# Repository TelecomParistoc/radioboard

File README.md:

# RadioBoard

Design d'une carte électronique permettant de d'échanger des messages et de localiser les robots

## Définition des acteurs

On distingue 3 types d'acteurs aux besoins différents :

* les robots, où la radio se comporte comme un esclave piloté par le raspberry pi et autres composants
* les balise sur les robots adverses, où la radio est indépendante et doit envoyer les mesures aux robots
* les balises fixes, où la radio est indépendante et peut communiquer avec un ordinateur pour le debug

Pour des raisons d'efficacité, il a été décidé de ne concevoir qu'une seule carte, adaptée aux besoins de tous les acteurs.

## Vue système

### Système robot

Il est nécessaire de fournir 3 ports :

* Un port esclave sur le bus I2C principal du robot, permettant la communication avec le Raspberry Pi
* Un port esclave SPI pour une liaison direct rapide à faible latence avec la carte de contrôle des moteurs
* Un port série pour ouvrir un terminal série à distance sur le Raspberry Pi contrôlé depuis une balise fixe en cas de perte de la connexion WiFi (environnement difficile pendant la coupe)

Par ailleurs, l'alimentation qui sera fournie à la carte sera du 5V (en raison de la consommation importante des Decawaves, il est plus raisonnable de ne pas tirer sur le 3.3V du Raspberry Pi), elle devra donc être abaissée localement.

### Système balise

Dans les balises (fixes et sur les robots adverses), la carte radio est l'unique carte, et n'est accompagnée que d'une batterie. Elle doit donc être autonome.

La faisabilité d'un système interne de recharge doit être étudié. Dans tous les cas, le système doit pouvoir détecter la fin de décharge de la batterie afin d'éviter la destruction de celle-ci.

## Contraintes

#### RC1 Placement du module radio
Pour fonctionner correctement, le module radio DWM1000 doit être placé conformément aux contraintes de la datasheet du DWM1000 page 17.

#### RC2 Taille de la carte
Afin de pouvoir être embarqué dans les balises, la carte devra avoir des dimensions maximales de 70mmx70mm. De plus, il est important de minimiser la taille de la carte pour des raisons d'efficacité budgétaire. Il faut également prévoir le placement des batteries pour les balises, afin que le système total rentre dans un pavé de 80x80x80mm comme spécifié dans le règlement de la coupe de France de robotique.

#### RC3 Placement des connecteurs
Tout les connecteurs devront être placés de telle sorte qu'un câble connecté ne puisse pas se mettre dans le chemin du signal radio entre deux modules.

#### RC4 Programmation et debug de la carte
La programmation et le debug des cartes sera fait avec les sondes J-link du club en SWD et devra utiliser un connecteur comme [celui-ci](http://fr.farnell.com/samtec/shf-105-01-l-d-sm/embase-male-1-27mm-2x5-voies/dp/1885915).

#### RC5 Alimentation de la carte
L'alimentation de la carte se fera dans les robots en 5VDC et dans les balises directement depuis les batteries sans composant extérieur.

#### RC6 Technologie des batteries
Le règlement de la coupe de France de robotique interdit l'utilisation de batteries Li-Ion et Li-Po en dehors d'un sac de protection, dont les dimensions rendront l'intégration dans des balises difficile. Ces deux technologies sont donc exclues.

#### RC7 Configuration du connecteur I2C
Le connecteur I2C reliant la carte au bus principal et fournissant l'alimentation **5V** est un micromatch 6 pins et doit avoir la configuration suivante :

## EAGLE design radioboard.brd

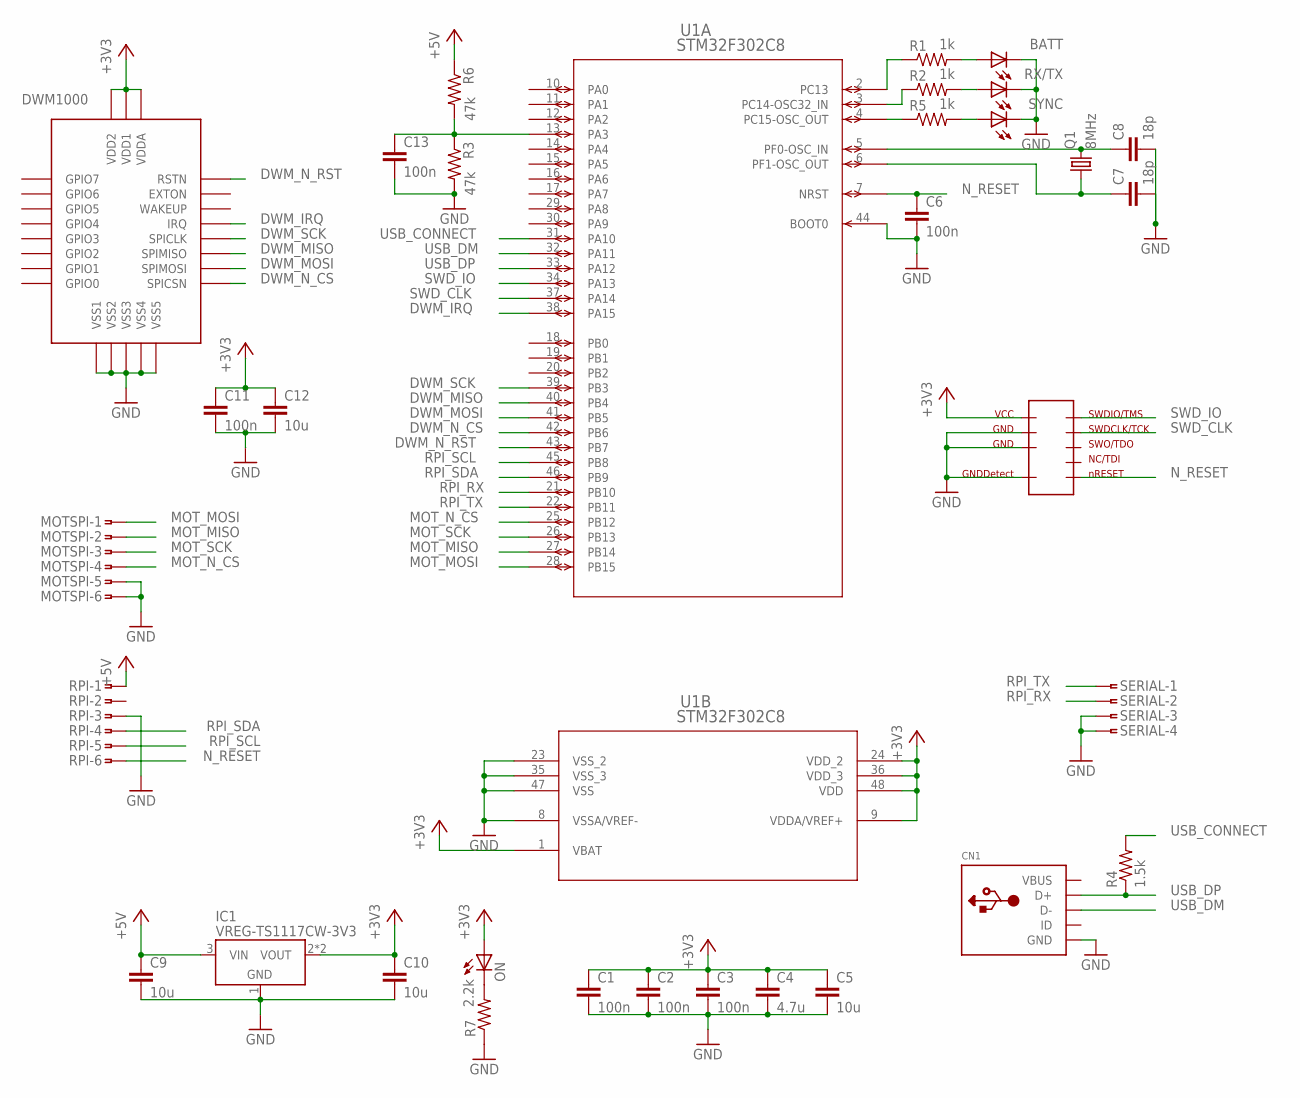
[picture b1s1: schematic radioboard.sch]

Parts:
BATT: LEDCHIPLED_0805; CHIPLED_0805
C1, C2, C3, C6, C11, C13: 100n; C0805
C4: 4.7u; C0805
C5, C9, C10, C12: 10u; C0805
C7, C8: 18p; C0805
CN1: USBMINIB; USB-MINIB
DWM1000: DWM1000; DW1000-PACKAGE
IC1: VREG-TS1117CW-3V3; SOT223
MOTSPI: SMDTOP-6; SMDTOP6
ON: LEDCHIPLED_0805; CHIPLED_0805
Q1: 8MHz; SM49
R1, R2, R5: 1k; M0805
R3, R6: 47k; M0805
R4: 1.5k; M0805
R7: 2.2k; M0805
RPI: SMDTOP-6; SMDTOP6
RX/TX: LEDCHIPLED_0805; CHIPLED_0805
SERIAL: SMDTOP-4; SMDTOP4
SYNC: LEDCHIPLED_0805; CHIPLED_0805
U1: STM32F302C8; LQFP48-7X7MM
U$1: SWD/JTAG-_PINS; SAMTEC_SHF-105-01-L-D-SM

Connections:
+3V3: C1.1, C2.1, C3.1, C4.1, C5.1, C10.1, C11.1, C12.1, DWM1000.VDD3V3 (VDD1), DWM1000.VDD3V32 (VDD2), DWM1000.VDDAON (VDDA), IC1.2 (VOUT), IC1.4 (VOUT), ON.A, U1.1 (VBAT), U1.9 (VDDA/VREF+), U1.24 (VDD_2), U1.36 (VDD_3), U1.48 (VDD), U$1.P$1
+5V: C9.1, IC1.3 (VIN), R6.1, RPI.1
DWM_IRQ: DWM1000.IRQ, U1.38 (PA15)
DWM_MISO: DWM1000.SPIMISO, U1.40 (PB4)
DWM_MOSI: DWM1000.SPIMOSI, U1.41 (PB5)
DWM_N_CS: DWM1000.SPICSN, U1.42 (PB6)
DWM_N_RST: DWM1000.RSTN, U1.43 (PB7)
DWM_SCK: DWM1000.SPICLK, U1.39 (PB3)
GND: BATT.C, C1.2, C2.2, C3.2, C4.2, C5.2, C6.2, C7.2, C8.2, C9.2, C10.2, C11.2, C12.2, C13.2, CN1.GND, DWM1000.VSS1, DWM1000.VSS2, DWM1000.VSS3, DWM1000.VSS4, DWM1000.VSS5, IC1.1 (GND), MOTSPI.5, MOTSPI.6, R3.2, R7.1, RPI.3, RX/TX.C, SERIAL.3, SERIAL.4, SYNC.C, U1.8 (VSSA/VREF-), U1.23 (VSS_2), U1.35 (VSS_3), U1.44 (BOOT0), U1.47 (VSS), U$1.P$3, U$1.P$5, U$1.P$9
MOT_MISO: MOTSPI.2, U1.27 (PB14)
MOT_MOSI: MOTSPI.1, U1.28 (PB15)
MOT_N_CS: MOTSPI.4, U1.25 (PB12)
MOT_SCK: MOTSPI.3, U1.26 (PB13)
unnamed: R1.1, U1.2 (PC13)
unnamed: C7.1, Q1.1, U1.6 (PF1-OSC_OUT)
unnamed: C8.1, Q1.2, U1.5 (PF0-OSC_IN)
unnamed: R2.1, U1.3 (PC14-OSC32_IN)
unnamed: R5.1, U1.4 (PC15-OSC_OUT)
unnamed: BATT.A, R1.2
unnamed: R2.2, RX/TX.A
unnamed: C13.1, R3.1, R6.2, U1.13 (PA3)
unnamed: ON.C, R7.2
unnamed: R5.2, SYNC.A
N_RESET: C6.1, RPI.6, U1.7 (NRST), U$1.P$10
RPI_RX: SERIAL.2, U1.21 (PB10)
RPI_SCL: RPI.5, U1.45 (PB8)
RPI_SDA: RPI.4, U1.46 (PB9)
RPI_TX: SERIAL.1, U1.22 (PB11)
SWD_CLK: U1.37 (PA14), U$1.P$4
SWD_IO: U1.34 (PA13), U$1.P$2
USB_CONNECT: R4.2, U1.31 (PA10)
USB_DM: CN1.D-, U1.32 (PA11)
USB_DP: CN1.D+, R4.1, U1.33 (PA12)
VBUS: CN1.VBUS

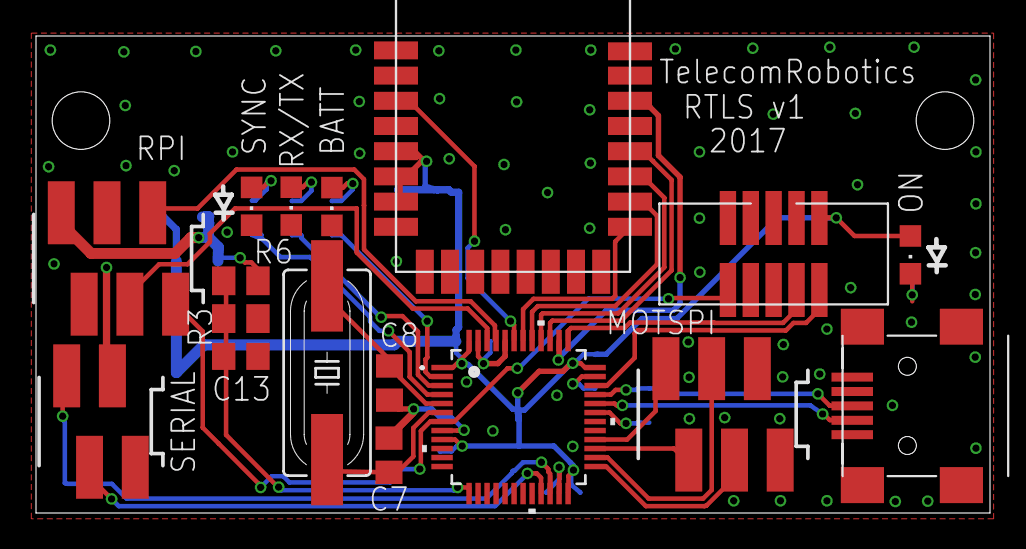
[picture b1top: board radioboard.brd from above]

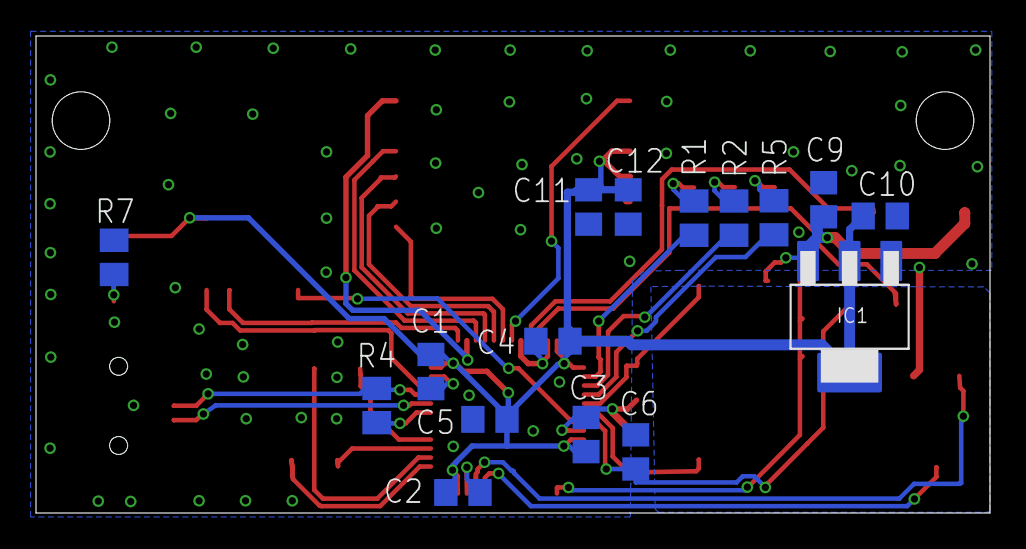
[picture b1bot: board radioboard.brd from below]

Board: 2 copper layers, 53.0 x 26.5 mm, 33 parts (16 on the bottom side), 33 nets.

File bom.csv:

Qty,Qty to buy,Value,Device,Package,Parts,Description, Farnell reference
4,0,,LEDCHIPLED_0805,CHIPLED_0805,BATT ON RX/TX SYNC,LED,/
1,0,,SMDTOP-4,SMDTOP4,SERIAL,AMP connector,/
2,0,,SMDTOP-6,SMDTOP6,MOTSPI RPI,AMP connector,/
1,0,1.5k,R-US_M0805,M0805,R4,RESISTOR,/
6,0,100n,C-EUC0805,C0805,C1 C2 C3 C6 C11 C13,CAPACITOR,/
4,0,10u,C-EUC0805,C0805,C5 C9 C10 C12,CAPACITOR,/
3,0,1k,R-US_M0805,M0805,R1 R2 R5,RESISTOR,/
1,0,2.2k,R-US_M0805,M0805,R7,RESISTOR,/
1,0,4.7u,C-EUC0805,C0805,C4,CAPACITOR,/
2,0,47k,R-US_M0805,M0805,R3 R6,RESISTOR,/
1,0,8MHz,CRYSTALSM49,SM49,Q1,CRYSTAL,/
1,0,DWM1000,DWM1000,DW1000-PACKAGE,DWM1000,,/
1,0,STM32F302C8,STM32F302_303C2,LQFP48-7X7MM,U1,,/
1,0,SWD/JTAG-_PINS,SWD/JTAG-_PINS,SAMTEC_SHF-105-01-L-D-SM,U$1,,/
1,0,VREG-TS1117CW-3V3,VREG-TS1117CW-3V3,SOT223,IC1,Voltage Regulator,/
1,1,,USBMINIB,USB-MINIB,CN1,USB Connectors,2112367
2,2,18p,C-EUC0805,C0805,C7 C8,CAPACITOR,1759056

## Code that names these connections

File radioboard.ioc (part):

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Mcu.Name=STM32F302C(6-8)Tx
Mcu.Package=LQFP48
Mcu.UserName=STM32F302C8Tx
PA10.GPIOParameters=GPIO_Label
PA10.GPIO_Label=USB_CONNECT
PA10.Signal=GPIO_Output
PA11.Mode=Device
PA11.Signal=USB_DM
PA12.Mode=Device
PA12.Signal=USB_DP
PA13.Mode=Serial_Wire
PA13.Signal=SYS_JTMS-SWDIO
PA14.Mode=Serial_Wire
PA14.Signal=SYS_JTCK-SWCLK
PA15.GPIOParameters=GPIO_Label
PA15.GPIO_Label=DWM_IRQ
PA15.Signal=GPIO_Output
PA3.GPIOParameters=GPIO_Label
PA3.GPIO_Label=VBAT_PROBE
PA3.Mode=IN4-Single-Ended
PA3.Signal=ADC1_IN4
PB10.Mode=Asynchronous
PB10.Signal=USART3_TX
PB11.Mode=Asynchronous
PB11.Signal=USART3_RX
PB12.Mode=NSS_Signal_Hard_Input
PB12.Signal=SPI2_NSS
PB13.Mode=Full_Duplex_Slave
PB13.Signal=SPI2_SCK
PB14.Mode=Full_Duplex_Slave
PB14.Signal=SPI2_MISO
PB15.Mode=Full_Duplex_Slave
PB15.Signal=SPI2_MOSI
PB3.Mode=Full_Duplex_Master
PB3.Signal=SPI3_SCK
PB4.Mode=Full_Duplex_Master
PB4.Signal=SPI3_MISO
PB5.Mode=Full_Duplex_Master
PB5.Signal=SPI3_MOSI
PB6.GPIOParameters=GPIO_Label
PB6.GPIO_Label=SPI3_nCS
PB6.Signal=GPIO_Input
PB7.GPIOParameters=GPIO_Label
PB7.GPIO_Label=DWM_RST
PB7.Signal=GPIO_Output
PB8.Mode=I2C
PB8.Signal=I2C1_SCL
PB9.Mode=I2C
PB9.Signal=I2C1_SDA
PC13.GPIOParameters=GPIO_Label
PC13.GPIO_Label=STAT3
PC13.Signal=GPIO_Output
PC14\ -\ OSC32_IN.GPIOParameters=GPIO_Label
PC14\ -\ OSC32_IN.GPIO_Label=STAT2
PC14\ -\ OSC32_IN.Signal=GPIO_Output
PC15\ -\ OSC32_OUT.GPIOParameters=GPIO_Label
PC15\ -\ OSC32_OUT.GPIO_Label=STAT1
PC15\ -\ OSC32_OUT.Signal=GPIO_Output
PF0-OSC_IN.Mode=HSE-External-Oscillator
PF0-OSC_IN.Signal=RCC_OSC_IN
PF1-OSC_OUT.Mode=HSE-External-Oscillator
PF1-OSC_OUT.Signal=RCC_OSC_OUT
RCC.HSEPLLFreq_Value=8000000
RCC.HSE_VALUE=8000000
RCC.SYSCLKFreq_VALUE=8000000

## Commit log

2017-02-22 added robot architecture
2017-02-22 added robot architecture in README
2017-02-25 added beacon architecture
2017-02-25 added beacon architecture diagram and constraints
2017-02-25 added datasheets
2017-02-26 battery technologies
2017-03-04 added I2C connector drawing
2017-03-04 smaller I2C connector
2017-03-04 added RC7
2017-03-04 upper case mess
2017-03-08 added libraries as submodule
2017-03-14 Add the list of componants
2017-04-01 started schematic and board
2017-04-01 added 3.3V LDO regulator datasheet
2017-04-01 finished schematic, continued placing
2017-04-03 placed and routed PCB, added design rules
2017-04-04 finished PCB
2017-04-04 added pdf of board and schematic
2017-05-16 added bom

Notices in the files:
parts and their libraries:
COPYRIGHT: Copyright C 2016 Accelerated Designs. All rights reserved
